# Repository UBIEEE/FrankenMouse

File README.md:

# FrankenMouse

## Introduction

_FrankenMouse_ is a MicroMouse robot that was designed, built, and programmed from scratch by members of the University at Buffalo's IEEE Student Branch.

Some might say that our robot resembles one of Dr. Victor Frankenstein's creations - smaller and more agile, yet equally terrifying. Thus, the name _FrankenMouse_ was born.

### Objective

The objective of a MicroMouse robot is to autonomously nativate and solve a 16x16 maze as fast as possible. To learn more about the MicroMouse competition, check out the excellent [Veritasium Video](https://youtu.be/ZMQbHMgK2rw) on the topic.

## Team

#### Current Collaborators (Versions 2+3):

- [Peter Lilley](https://github.com/petelilley)
  - PCB designs, V2+3 mechanical designs, soldering, 3D printing, assembly, software
- [Eric Butcher](https://github.com/Eric-Butcher)
  - Solver algorithms

#### Former Collaborators (Version 1):

- Dylan Taton
  - V1 mechanical design
- [Sam Chen](https://github.com/SamChen1738)
  - FloodFill algorithm desktop simulation ([MicroMouseSimulator](https://github.com/UBIEEE/MicroMouseSimulator))

## Specs

| Name                | FrankenMouse V2+3                                 |
|-|-|
| Length/Width/Height | 10cm/7cm/3.5cm                                    |
| Weight              | 69 g (w/o batt), 92 g (w/ batt)                   |
| MCU                 | STM32WB55CGU6                                     |
| Motors              | 6V Micro Metal Gearmotor (20:1)                   |
| Encoders            | Micro Metal Motor Encoder (6 pole magnetic discs) |
| Motor Driver        | DRV8835                                           |
| IR Sensors          | SFH4545 (Emitter) + TEFT4300 (Receiver)           |
| IMU                 | ICM-42670-P                                       |
| Tire Diameter       | 2.5 cm                                            |
| Buzzer              | PS1240P02BT                                       |
| Battery             | 2S 450 mAh Li-Po                                  |
| Voltage Regulator   | TPS564208DDCR                                     |
| Connectivity        | SWD, BLE, USB-C (V2 only)                         |

## Robot Versions

- Version 1
  - Custom PCB was designed and manufactured. Assembly problems led to the decision to redesign the robot
- Version 2 (Green PCB)
  - Conceptually different PCB design from V1. Smaller, more compact robot, and better cohesion between PCB and mechanical design
  - Fully assembled and functional robot
- Version 3 (Blue PCB)
  - Minor revisions to V2 PCB including:
    - Fixed the incorrect motor driver wiring to MCU (enable proper hardware PWM control instead of software PWM)
    - Adjusted IR sensor angles for better wall detection
    - Got rid of annoying JST motor/encoder connectors on PCB in favor of simple pin headers
    - Moved SWD connector to not interfere with buttons
    - Removed USB-C connector (not necessary)
    - Added an LED

## Repository Structure

- [`firmware/`](firmware/) - Software running on the robot
- [`hardware/`](hardware/) - PCB designs and mechanical CAD files
- [`simulation/`](simulation/) - Godot-based desktop 3D simulation of the robot
- [`app/`](app/) - iOS/macOS app for controlling the robot over BLE
- [`cli/`](cli/) - Custom interactive shell with command-line tools for controlling the robot over BLE
- [`ti84_controller`](ti84_controller/) - (Silly) TI-84 Plus CE program that communicates with the CLI over a serial connection, used to control the robot

## Gallery

Version 3:

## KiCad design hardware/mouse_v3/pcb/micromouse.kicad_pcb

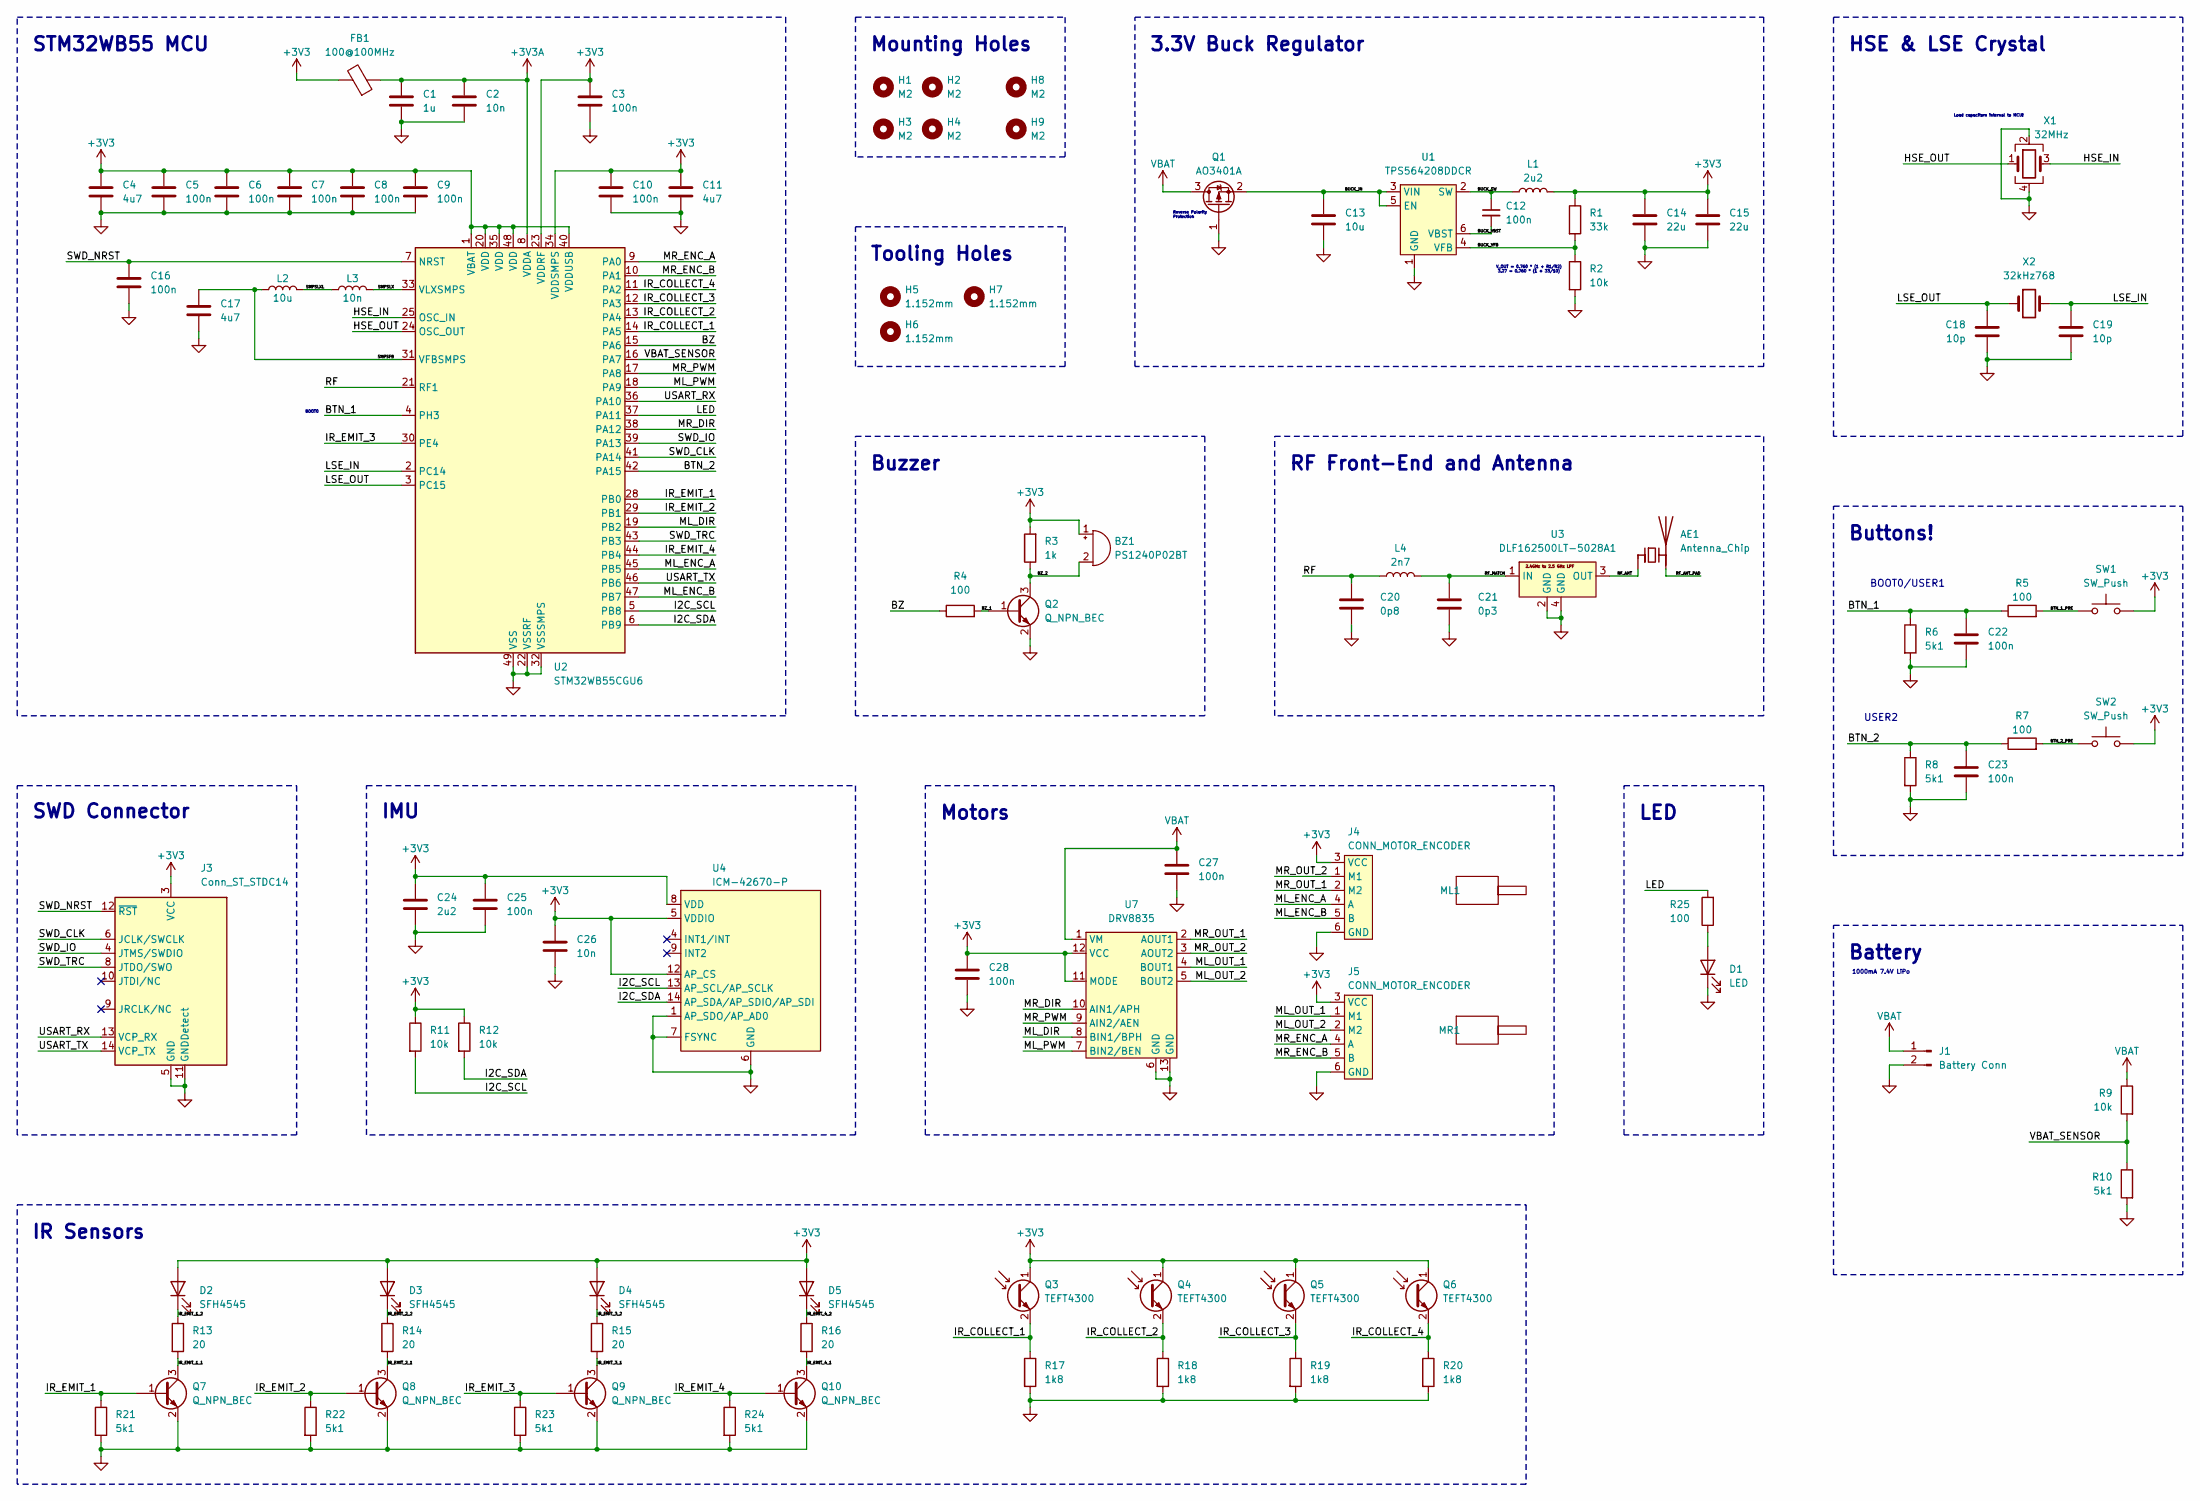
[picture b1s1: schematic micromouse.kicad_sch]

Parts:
AE1: Antenna_Chip; ANT_2450AT42A100E
BZ1: PS1240P02BT
C1: 1u; C_0603_1608Metric; LCSC Part C15849
C2, C26: 10n; C_0402_1005Metric; LCSC Part C15195
C3, C5, C6, C7, C8, C9, C10, C12, C16, C22, C23, C25, C27, C28: 100n; C_0402_1005Metric; LCSC Part C307331
C4, C11, C17: 4u7; C_0603_1608Metric; LCSC Part C19666
C13: 10u; C_1206_3216Metric; LCSC Part C13585
C14, C15: 22u; C_0805_2012Metric; LCSC Part C45783
C18, C19: 10p; C_0402_1005Metric; LCSC Part C32949
C20: 0p8; C_0402_1005Metric; LCSC Part C76915
C21: 0p3; C_0402_1005Metric; LCSC Part C92338
C24: 2u2; C_0603_1608Metric; LCSC Part C23630
D1: LED; D_0603_1608Metric; LCSC Part C2286
D2, D4: SFH4545; SFH4545_FLIPPED
D3, D5: SFH4545
FB1: 100@100MHz; D_0805_2012Metric; LCSC Part C1015
H1, H2, H3, H4, H8, H9: M2; MountingHole_2.2mm_M2
H5, H6, H7: 1.152mm; JLC_TOOLING_HOLE
J1: Battery Conn; CONN_BATTERY
J3: Conn_ST_STDC14; SAMTEC_FTSH-107-01-L-DV-K-A
J4, J5: CONN_MOTOR_ENCODER; PinHeader_1x06_P2.00mm_Vertical
L1: 2u2; L_0805_2012Metric; LCSC Part C383369
L2: 10u; L_0805_2012Metric; LCSC Part C1046
L3: 10n; L_0402_1005Metric; LCSC Part C77103
L4: 2n7; L_0402_1005Metric; LCSC Part C77108
ML1: MOTOR_N20
MR1: MOTOR_N20
Q1: AO3401A; SOT-23; LCSC Part C15127
Q2, Q7, Q8, Q9, Q10: Q_NPN_BEC; SOT-23; LCSC Part C2150
Q3, Q5: TEFT4300
Q4, Q6: TEFT4300; TEFT4300_FLIPPED
R1: 33k; R_0402_1005Metric; LCSC Part C25779
R2, R9, R11, R12: 10k; R_0402_1005Metric; LCSC Part C25744
R3: 1k; R_0402_1005Metric; LCSC Part C11702
R4, R5, R7, R25: 100; R_0402_1005Metric; LCSC Part C25076
R6, R8, R10, R21, R22, R23, R24: 5k1; R_0402_1005Metric; LCSC Part C25905
R13, R14, R15, R16: 20; R_1206_3216Metric; LCSC Part C17955
R17, R18, R19, R20: 1k8; R_0603_1608Metric; LCSC Part C4177
SW1, SW2: SW_Push; SW_PUSH_1P1T_6x3.5mm_H5.0_APEM_MJTP1250
U1: TPS564208DDCR; TSOT-23-6; LCSC Part C486062
U2: STM32WB55CGU6; QFN-48-1EP_7x7mm_P0.5mm_EP5.6x5.6mm; LCSC Part C404023
U3: DLF162500LT-5028A1; LCSC Part C531364
U4: ICM-42670-P; LCSC Part C3288646
U7: DRV8835; DSS0012A; LCSC Part C129328
X1: 32MHz; XL7EL89CKI-111YLC-32M; LCSC Part C2965582
X2: 32kHz768; Crystal_SMD_3215-2Pin_3.2x1.5mm; LCSC Part C32346

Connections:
+3V3: BZ1.1 (+), C3.1, C4.1, C5.1, C6.1, C7.1, C8.1, C9.1, C10.1, C11.1, C14.1, C15.1, C24.1, C25.1, C26.1, C28.1, D2.2 (A), D3.2 (A), D4.2 (A), D5.2 (A), FB1.2, J3.3 (VCC), J4.3 (VCC), J5.3 (VCC), L1.2, Q3.1 (C), Q4.1 (C), Q5.1 (C), Q6.1 (C), R1.1, R3.2, R11.1, R12.1, SW1.2, SW2.2, U2.1 (VBAT), U2.20 (VDD), U2.23 (VDDRF), U2.34 (VDDSMPS), U2.35 (VDD), U2.40 (VDDUSB), U2.48 (VDD), U4.5 (VDDIO), U4.8 (VDD), U4.12 (AP_CS), U7.11 (MODE), U7.12 (VCC)
+3V3A: C1.1, C2.1, FB1.1, U2.8 (VDDA)
/BTN_1: C22.1, R5.1, R6.1, U2.4 (PH3)
/BTN_1_PRE: R5.2, SW1.1
/BTN_2: C23.1, R7.1, R8.1, U2.42 (PA15)
/BTN_2_PRE: R7.2, SW2.1
/BUCK_IN: C13.1, Q1.2 (S), U1.3 (VIN), U1.5 (EN)
/BUCK_SW: C12.1, L1.1, U1.2 (SW)
/BUCK_VBST: C12.2, U1.6 (VBST)
/BUCK_VFB: R1.2, R2.1, U1.4 (VFB)
/BZ: R4.1, U2.15 (PA6)
/BZ_1: Q2.1 (B), R4.2
/BZ_2: BZ1.2 (-), Q2.3 (C), R3.1
/HSE_IN: U2.25 (OSC_IN), X1.3
/HSE_OUT: U2.24 (OSC_OUT), X1.1
/I2C_SCL: R11.2, U2.5 (PB8), U4.13 (AP_SCL/AP_SCLK)
/I2C_SDA: R12.2, U2.6 (PB9), U4.14 (AP_SDA/AP_SDIO/AP_SDI)
/IR_COLLECT_1: Q3.2 (E), R17.1, U2.14 (PA5)
/IR_COLLECT_2: Q4.2 (E), R18.1, U2.13 (PA4)
/IR_COLLECT_3: Q5.2 (E), R19.1, U2.12 (PA3)
/IR_COLLECT_4: Q6.2 (E), R20.1, U2.11 (PA2)
/IR_EMIT_1: Q7.1 (B), R21.1, U2.28 (PB0)
/IR_EMIT_1_1: Q7.3 (C), R13.2
/IR_EMIT_1_2: D2.1 (K), R13.1
/IR_EMIT_2: Q8.1 (B), R22.1, U2.29 (PB1)
/IR_EMIT_2_1: Q8.3 (C), R14.2
/IR_EMIT_2_2: D3.1 (K), R14.1
/IR_EMIT_3: Q9.1 (B), R23.1, U2.30 (PE4)
/IR_EMIT_3_1: Q9.3 (C), R15.2
/IR_EMIT_3_2: D4.1 (K), R15.1
/IR_EMIT_4: Q10.1 (B), R24.1, U2.44 (PB4)
/IR_EMIT_4_1: Q10.3 (C), R16.2
/IR_EMIT_4_2: D5.1 (K), R16.1
/LED: R25.2, U2.37 (PA11)
/LSE_IN: C19.1, U2.2 (PC14), X2.2
/LSE_OUT: C18.1, U2.3 (PC15), X2.1
/ML_DIR: U2.19 (PB2), U7.8 (BIN1/BPH)
/ML_ENC_A: J4.4 (A), U2.45 (PB5)
/ML_ENC_B: J4.5 (B), U2.47 (PB7)
/ML_OUT_1: J5.1 (M1), U7.4 (BOUT1)
/ML_OUT_2: J5.2 (M2), U7.5 (BOUT2)
/ML_PWM: U2.18 (PA9), U7.7 (BIN2/BEN)
/MR_DIR: U2.38 (PA12), U7.10 (AIN1/APH)
/MR_ENC_A: J5.4 (A), U2.9 (PA0)
/MR_ENC_B: J5.5 (B), U2.10 (PA1)
/MR_OUT_1: J4.2 (M2), U7.2 (AOUT1)
/MR_OUT_2: J4.1 (M1), U7.3 (AOUT2)
/MR_PWM: U2.17 (PA8), U7.9 (AIN2/AEN)
/RF: C20.1, L4.2, U2.21 (RF1)
/RF_ANT: AE1.1 (FEED), U3.3 (OUT)
/RF_ANT_PAD: AE1.2 (PCB_Trace)
/RF_MATCH: C21.1, L4.1, U3.1 (IN)
/SMPSFB: C17.1, L2.1, U2.31 (VFBSMPS)
/SMPSLX: L3.2, U2.33 (VLXSMPS)
/SMPSLXL: L2.2, L3.1
/SWD_CLK: J3.6 (JCLK/SWCLK), U2.41 (PA14)
/SWD_IO: J3.4 (JTMS/SWDIO), U2.39 (PA13)
/SWD_NRST: C16.1, J3.12 (~RST), U2.7 (NRST)
/SWD_TRC: J3.8 (JTDO/SWO), U2.43 (PB3)
/USART_RX: J3.13 (VCP_RX), U2.36 (PA10)
/USART_TX: J3.14 (VCP_TX), U2.46 (PB6)
/VBAT_SENSOR: R9.2, R10.1, U2.16 (PA7)
GND: C1.2, C2.2, C3.2, C4.2, C5.2, C6.2, C7.2, C8.2, C9.2, C10.2, C11.2, C13.2, C14.2, C15.2, C16.2, C17.2, C18.2, C19.2, C20.2, C21.2, C22.2, C23.2, C24.2, C25.2, C26.2, C27.2, C28.2, D1.1 (K), J1.2, J3.5 (GND), J3.7 (GND), J3.11 (GNDDetect), J4.6 (GND), J5.6 (GND), Q1.1 (G), Q2.2 (E), Q7.2 (E), Q8.2 (E), Q9.2 (E), Q10.2 (E), R2.2, R6.2, R8.2, R10.2, R17.2, R18.2, R19.2, R20.2, R21.2, R22.2, R23.2, R24.2, U1.1 (GND), U2.22 (VSSRF), U2.32 (VSSSMPS), U2.49 (VSS), U3.2 (GND), U3.4 (GND), U4.1 (AP_SDO/AP_AD0), U4.6 (GND), U4.7 (FSYNC), U7.6 (GND), U7.13 (GND), X1.2, X1.4
unnamed: D1.2 (A), R25.1
VBAT: C27.1, J1.1, Q1.3 (D), R9.1, U7.1 (VM)

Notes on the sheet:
Buzzer
SWD Connector
BOOT0/USER1
Tooling Holes
RF Front-End and Antenna
IR Sensors
Buttons!
Reverse Polarity Protection
STM32WB55 MCU
LED
V_OUT = 0.760 * (1 + R1/R2) 3.27 = 0.760 * (1 + 33/10)
HSE & LSE Crystal
IMU
3.3V Buck Regulator
1000mA 7.4V LiPo
Motors
Mounting Holes
Battery
USER2
BOOT0
Load capacitors internal to MCU!

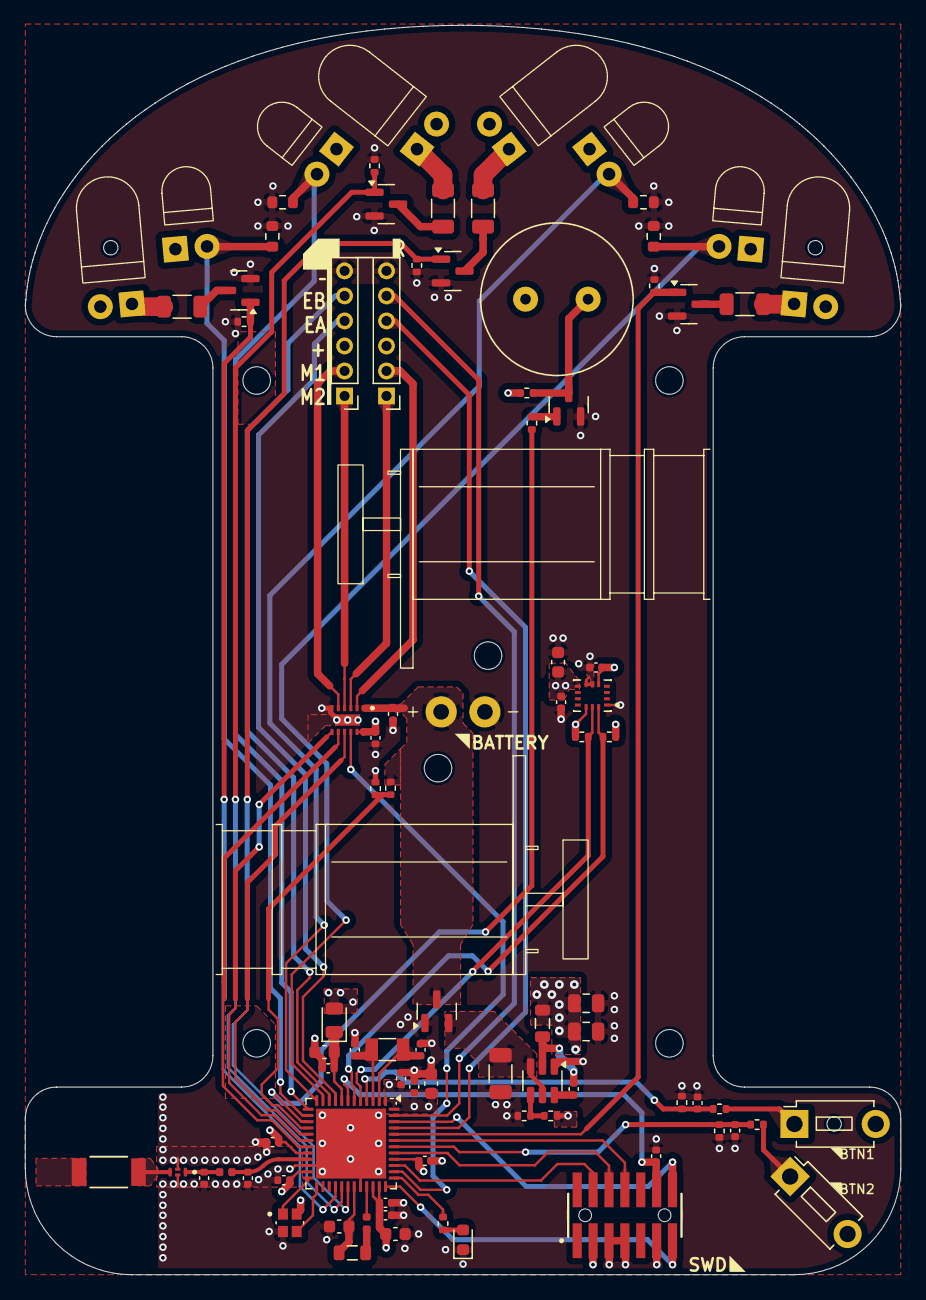
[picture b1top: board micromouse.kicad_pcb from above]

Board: 4 copper layers, 70.0 x 99.9 mm, 99 parts (0 on the bottom side), 64 nets.

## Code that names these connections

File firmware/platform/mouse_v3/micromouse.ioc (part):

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Mcu.Name=STM32WB55CGUx
Mcu.Package=UFQFPN48
Mcu.UserName=STM32WB55CGUx
PA0.GPIOParameters=GPIO_Label
PA0.GPIO_Label=ENCODER_RIGHT_A
PA0.Signal=S_TIM2_CH1
PA1.GPIOParameters=GPIO_Label
PA1.GPIO_Label=ENCODER_RIGHT_B
PA1.Signal=S_TIM2_CH2
PA10.Mode=Asynchronous
PA10.Signal=USART1_RX
PA11.GPIOParameters=GPIO_Label
PA11.GPIO_Label=LED
PA11.Signal=GPIO_Output
PA12.GPIOParameters=GPIO_Label
PA12.GPIO_Label=MOTOR_LEFT_DIR
PA12.Signal=GPIO_Output
PA13.Mode=Trace_Asynchronous_SW
PA13.Signal=SYS_JTMS-SWDIO
PA14.Mode=Trace_Asynchronous_SW
PA14.Signal=SYS_JTCK-SWCLK
PA15.GPIOParameters=GPIO_Label
PA15.GPIO_Label=BUTTON_2
PA15.Signal=GPXTI15
PA2.GPIOParameters=GPIO_Label
PA2.GPIO_Label=IR_FAR_RIGHT_COLLECT
PA2.Signal=ADCx_IN7
PA3.GPIOParameters=GPIO_Label
PA3.GPIO_Label=IR_MID_RIGHT_COLLECT
PA3.Signal=ADCx_IN8
PA4.GPIOParameters=GPIO_Label
PA4.GPIO_Label=IR_MID_LEFT_COLLECT
PA4.Signal=ADCx_IN9
PA5.GPIOParameters=GPIO_Label
PA5.GPIO_Label=IR_FAR_LEFT_COLLECT
PA5.Signal=ADCx_IN10
PA6.GPIOParameters=GPIO_ModeDefaultPP,GPIO_Speed,GPIO_PuPd,GPIO_Label
PA6.GPIO_Label=BUZZER
PA6.GPIO_ModeDefaultPP=GPIO_MODE_AF_PP
PA6.GPIO_PuPd=GPIO_NOPULL
PA6.GPIO_Speed=GPIO_SPEED_FREQ_LOW
PA6.Signal=S_TIM16_CH1
PA7.GPIOParameters=GPIO_Label
PA7.GPIO_Label=VOLTAGE_IN
PA7.Signal=ADCx_IN12
PA8.GPIOParameters=GPIO_Label
PA8.GPIO_Label=MOTOR_LEFT
PA8.Signal=S_TIM1_CH1
PA9.GPIOParameters=GPIO_Label
PA9.GPIO_Label=MOTOR_RIGHT
PA9.Signal=S_TIM1_CH2
PB0.GPIOParameters=GPIO_Label
PB0.GPIO_Label=IR_FAR_LEFT_EMIT
PB0.Signal=GPIO_Output
PB1.GPIOParameters=GPIO_Label
PB1.GPIO_Label=IR_MID_LEFT_EMIT
PB1.Signal=GPIO_Output
PB2.GPIOParameters=GPIO_Label
PB2.GPIO_Label=MOTOR_RIGHT_DIR
PB2.Signal=GPIO_Output
PB3.Mode=Trace_Asynchronous_SW
PB3.Signal=SYS_JTDO-SWO
PB4.GPIOParameters=GPIO_Label
PB4.GPIO_Label=IR_FAR_RIGHT_EMIT
PB4.Signal=GPIO_Output
PB5.GPIOParameters=GPIO_Label
PB5.GPIO_Label=ENCODER_LEFT_B
PB5.Mode=Encoder_mode_occur1
PB5.Signal=LPTIM1_IN1
PB6.Mode=Asynchronous
PB6.Signal=USART1_TX
PB7.GPIOParameters=GPIO_Label
PB7.GPIO_Label=ENCODER_LEFT_A
PB7.Mode=Encoder_mode_occur1
PB7.Signal=LPTIM1_IN2
PB8.Mode=I2C
PB8.Signal=I2C1_SCL
PB9.Mode=I2C
PB9.Signal=I2C1_SDA
PC14-OSC32_IN.Mode=LSE-External-Oscillator
PC14-OSC32_IN.Signal=RCC_OSC32_IN
PC15-OSC32_OUT.Mode=LSE-External-Oscillator
PC15-OSC32_OUT.Signal=RCC_OSC32_OUT
PE4.GPIOParameters=GPIO_Label
PE4.GPIO_Label=IR_MID_RIGHT_EMIT
PE4.Signal=GPIO_Output
PH3-BOOT0.GPIOParameters=GPIO_Label
PH3-BOOT0.GPIO_Label=BUTTON_1
PH3-BOOT0.Signal=GPXTI3
RCC.HSE_VALUE=32000000
RCC.SYSCLKFreq_VALUE=64000000
RCC.SYSCLKSource=RCC_SYSCLKSOURCE_PLLCLK
board=custom

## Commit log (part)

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2025-01-31 Improved DriveController class, vision stuff, app things, etc.
2025-01-31 App icon designs
2025-03-22 A couple changes...
    Restructured firmware: split into platform-independent logic library and platform-specific hardware code. Created 3D simulation in Godot with ROS2, added ROS2 target to dashboard, and lots more.
2025-03-24 V3 PCB and CAD
2025-03-24 Created STM32CubeMX project for V3
2025-03-25 Changed from C++23 to C++20
2025-03-27 Mouse v2 Buttons
2025-03-27 Updated VSCode Mouse v3 include paths
2025-03-27 Mouse v3 hardware implementations
2025-04-29 Fixed BLE service discovery
2025-04-29 Disable optimizations in Debug
2025-04-29 Invert left motor direction
2025-04-29 Fixed silly typos in Feedback implementations
2025-04-29 Vision stuff
2025-04-29 Songs stop when told to
2025-04-29 Direction to string
2025-04-29 Started flood fill implementation, drive controller work, etc.
2025-04-30 Initialized CMakeLists for CLI tool
2025-05-05 Linked with isocline and SimpleBLE
2025-05-05 Created prompt using isocline, got completions and highlighting working :D
2025-05-05 Commands are now their own classes that conform to a CommandType concept
2025-05-06 Parsed arguments, added empty TI84Control command, help messages, etc.
2025-05-09 Thread-safe status, warning, and error message reporting
2025-05-09 Initialized SimpleBLE and connected to the MicroMouse
2025-05-09 Commands can now be constructed with BLEManager&, created RSSI command
2025-05-09 Fixed crash on empty prompt invocation
2025-05-10 Added dummy peripheral option
2025-05-10 Generated help messages for commands based on options, some command changes, integrated help command into prompt, etc.
2025-05-10 Added dummy option to shell usage
2025-05-10 Got rid of CMake warnings
2025-05-10 Started making controller program for the TI-84 Plus CE using srldrvce
2025-05-10 Implemented ti84-control command to read serial data from the calculator and display it
    Next step is to send the data over BLE
2025-05-10 ANSI escape code macros
2025-05-10 Added ChassisSpeeds struct, converted TI-84 serial message to chassis speeds, updated display function
2025-05-11 Implemented writing and receiving BLE characteristics
2025-05-13 Added text wrap functions, updated help messages to be fully auto generated, etc.
2025-05-13 Created song-play command
2025-05-13 Added chassis speeds BLE characteristic
2025-05-13 Added manual control chassis speeds task
2025-05-13 Finished implementing ti84-control command
2026-01-29 Happy New Year
2026-01-29 Update README, add new photos
2026-02-03 Organize navigation
2026-02-03 Added vscode settings json (with cmake configure args)
2026-02-03 Feedback updates (see wiki)
2026-02-03 Fix typos
2026-02-03 Make Coordinate constructors/casts explicit
2026-02-03 Explicit constructors
2026-02-03 Remove compiler flags that were causing problems
2026-02-09 [cli] Formatting and comment cleanup
2026-02-09 [cli] Improved command setup, removed macros
2026-02-09 [cli] Added ROS2 support
2026-02-09 [cli] Improved how commands end
2026-02-09 [cli] Improved how main task feedback topic is handled
2026-02-09 [cli] Adjusted help messages
2026-02-09 [cli] Created task-run command
2026-02-15 [cli] Added init and end functions to Command
2026-02-15 [cli] Renamed CommunicationManager method process_events -> process_connection because that's what it does
2026-02-15 [cli] Created drive-pid-get and drive-pid-set commands
2026-02-15 [cli] Forgot to spin the ros2 node, fixed it now
2026-02-16 [firmware] Added units and gcem libraries
2026-02-16 [firmware] Switched units library default data type to float
2026-02-16 [firmware] Added mm/s and mm/s^2 unit declarations to units library
2026-02-16 [firmware] Revise building instructions in README
2026-02-16 [firmware] Updated clang-format
2026-02-16 [firmware] Integrated units library into firmware and improved trapezoid profile class
2026-03-01 [firmware] VSCode settings
2026-03-01 [cli] Send Drive PID values to -1 when not set
2026-03-01 [app] Get rid of warning
2026-03-01 [app] Default Drive PID values to -1
2026-03-01 [firmware] Mostly feedback updates to make consistent with other tools
2026-03-01 [simulation] Updated to Godot version 4.6
2026-03-01 [firmware] Added spdlog v1.17.0 thirdparty library
2026-03-01 [firmware] Link spdlog when building for desktop simulation
2026-03-01 [firmware] Setup logging
2026-03-05 [cli] Update tasks
2026-03-05 [cli] Make task-run and song-play commands wait for task/song to change before ending if keep alive is true
2026-03-05 [cli] Remove old ROS2 topic publisher
2026-03-05 [app] Update tasks
2026-03-05 [firmware] Update compiler optimization settings
2026-03-05 [firmware] Add VSCode debug config to run simulation
2026-03-05 [firmware] Floodfill implementation
2026-03-05 [firmware] Increase v3 track width measurement for added gears
2026-03-05 [firmware] Fix simulation feedback subscribers+publishers
2026-03-05 [firmware] Moved maze dimensions to Maze class
2026-03-05 [firmware] Removed unnecessary Song enum options
2026-03-05 [firmware] Updated vision wall detection, added functions to detect when side walls just disappeared
2026-03-05 [firmware] Implemented motion runner, updated tasks, improved navigation
2026-03-05 [firmware] Adjust speeds
2026-03-05 [firmware] Shorten update period
2026-03-05 [firmware] STM32 VS Code Extension update changed some settings
2026-03-05 [app] Fix incorrect BLE service UUIDs
2026-03-09 [firmware] Some drive updates
2026-03-09 [app] Added idle task and displayed encoder ticks on drive page
2026-03-09 [cli] Added idle task and updated motor data topic
2026-03-09 [firmware] Send maze cell data while navigating
2026-03-09 [cli] Added option to display maze when running task
2026-03-09 [firmware] Disable compiler abi notes caused by units library
2026-03-09 [firmware] Implemented v3 ADC code for IR sensors and battery voltage reading, sent battery voltage feedback
2026-03-09 [cli] Receive battery voltage feedback topic
2026-03-09 [app] Receive battery voltage feedback
2026-03-09 [firmware] Made the navigator end searching better
2026-03-12 [cli] Fix crash when invoking callback when receiving BLE data
2026-03-12 [firmware] The IR sensors were reversed!
2026-03-12 [simulation] Flip order of IR sensors array to match what robot expects
2026-03-12 [firmware] Reduced size of drive data BLE characteristic to be correct and get rid of warnings from the clients
2026-03-12 [firmware] Added task to run maze search with start-and-stop motions instead of smooth motion
2026-03-12 [app] Added task
2026-03-12 [cli] Added task
2026-03-12 [firmware] Remove all of the STM32 VSCode Extension generated files, updated build instructions to include setup instructions
2026-03-17 [firmware] Remove status feedback topic
2026-03-17 [firmware] Stop running current task when BLE disconnects
2026-03-17 [firmware] Errors
2026-03-17 [firmware] Zero IMU readings when entering standby mode
2026-03-18 [firmware] Calculate turn path length better by computing length of euler spiral segment. Cool stuff :D
2026-03-18 [firmware] Wait some time after taking IMU off standby mode to read data
2026-03-18 [firmware] Keep track of whether each direction of a cell has been seen instead of whether we have visited that cell
2026-03-18 [cli] Update cells to match firmware changes
2026-03-18 [firmware] Put goal endpoints back to normal
2026-03-20 [app] Display battery voltage on main page
2026-03-20 [firmware] Added get voltage method to battery class
2026-03-20 [firmware] Fix armed trigger side
2026-03-20 [firmware] Circular buffer class
2026-03-20 [firmware] Median filter class
2026-03-20 [firmware] Filter IMU gyro readings with median filter
2026-03-20 [firmware] Send time of errors
2026-03-20 [firmware] Status feedback is back
2026-03-21 [app] Status topics stuff
2026-03-21 [firmware] Two new drive tasks, rearranged task functions in robot class
2026-03-21 [app] New tasks
2026-03-21 [cli] Status topics and new tasks
2026-03-21 [firmware] Low pass filter on encoders to calculate better velocity
2026-03-21 [firmware] Adjust drive speeds based on battery voltage, add raw speed control function
2026-03-21 [firmware] Errors and status stuff
2026-03-21 [app] Status topic
2026-03-21 [firmware] Solve runs
2026-03-21 [firmware] Added Windows XP Shutdown Song on Error and fixed BLE shutdown Song.
2026-03-22 [firmware] Added IS_SIMULATION definition
2026-03-22 [firmware] Adjusted SIDE_WALL_OUT_OF_VIEW_SPOT to act good on real robot. Bad fix but ok for now
2026-03-22 [firmware] Is real function
2026-03-22 [firmware] Remove error during edge wall vision alignment
2026-03-22 [firmware] Made normal search not return to goal a second time, added task to do that if wanted
2026-03-22 [firmware] Speed up when solving during long straightaways
2026-03-22 [firmware] Drive backwards into wall for 180 degree turns (not really necessary, but might improve success rate I guess)
2026-03-22 [firmware] Improved turns I guess
2026-03-22 [firmware] Speeds
2026-03-22 [simulation] Test 5x5 maze
2026-03-22 [firmware] Don't vision align against wall edge if discrepancy is too big
2026-03-22 [firmware] Added solve with search navigation tasks
2026-03-22 [cli] Added tasks
2026-03-22 [firmware] Drive back to start after solve
2026-03-23 [firmware] Pre APEC adjustments
